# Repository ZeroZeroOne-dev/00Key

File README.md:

# 001Key

Custom 75% Keyboard.

## Hardware

- Teensy 4.1 development board
- SSD1306 0.96 Inch OLED Display
- MX & Alps switch support
- Backlight (single color) support
- RGB Underglow support

## Firmware

Custom firmware, has layer, OLED, Backlight, Underglow support

## OLED display

Displays currently shows

- capslock status
- Selected layer
- backlight intensity 
- Underglow collor selection (RGB Values)

## Underglow

3 Effects
- Solid color
- Rotating rainbow
- Off

## PCB

- Designed in kicad
- Used freerouting for traces

## Backplate

- Designed in FreeCAD
- Spaced from PCB with (10mm) standoffs
- STL files included for 3D printing in 2 parts

## Case

Stacked acrylic case

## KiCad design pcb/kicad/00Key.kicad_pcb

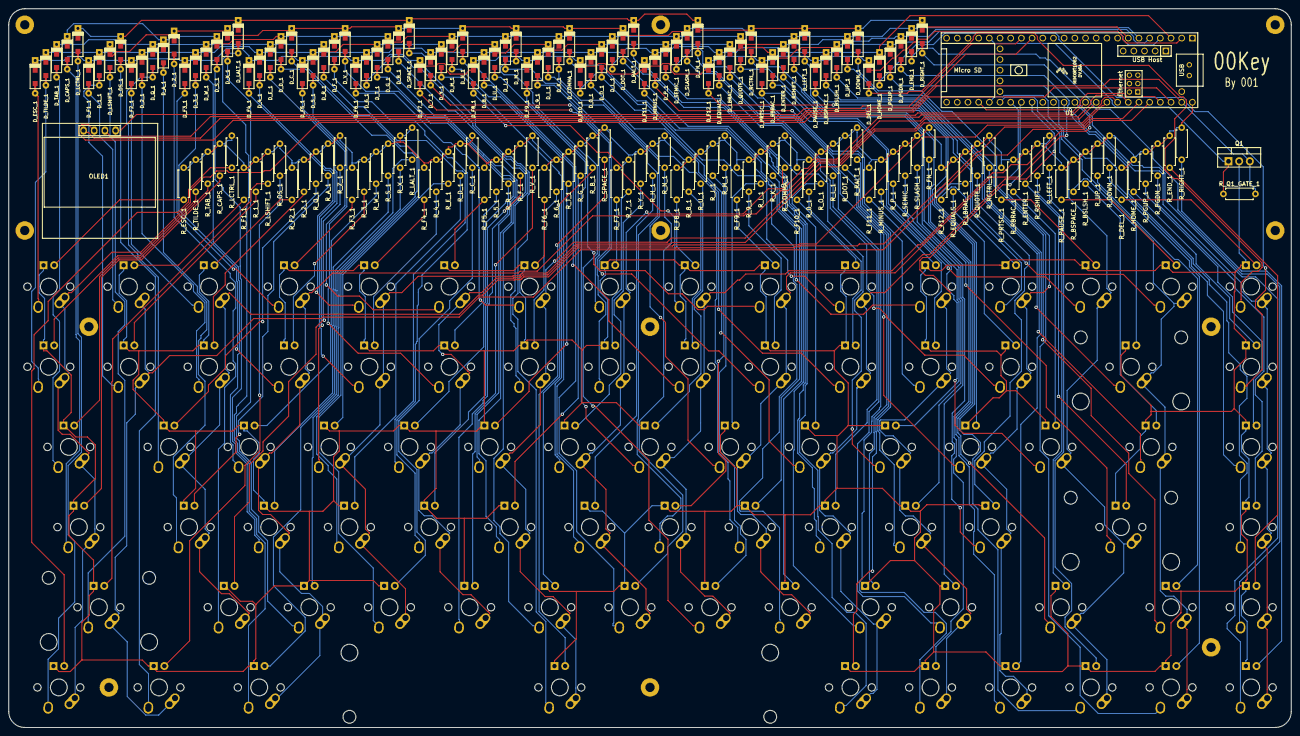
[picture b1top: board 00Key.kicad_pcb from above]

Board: 2 copper layers, 304.8 x 170.8 mm, 268 parts (0 on the bottom side), 197 nets.

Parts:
D_0_1, D_1_1, D_2_1, D_3_1, D_4_1, D_5_1, D_6_1, D_7_1, D_8_1, D_9_1: D; D_SOD123_axial
D_A_1: D; D_SOD123_axial
D_BSLSH_1: D; D_SOD123_axial
D_BSPACE_1: D; D_SOD123_axial
D_B_1: D; D_SOD123_axial
D_CAPS_1: D; D_SOD123_axial
D_COMMA_1: D; D_SOD123_axial
D_C_1: D; D_SOD123_axial
D_DEL_1: D; D_SOD123_axial
D_DOT_1: D; D_SOD123_axial
D_DOWN_1: D; D_SOD123_axial
D_D_1: D; D_SOD123_axial
D_END_1: D; D_SOD123_axial
D_ENTER_1: D; D_SOD123_axial
D_EQUALS_1: D; D_SOD123_axial
D_ESC_1: D; D_SOD123_axial
D_E_1: D; D_SOD123_axial
D_F1_1, D_F2_1, D_F3_1, D_F4_1, D_F5_1, D_F6_1, D_F7_1, D_F8_1, D_F9_1, D_F10_1, D_F11_1, D_F12_1: D; D_SOD123_axial
D_FN_1: D; D_SOD123_axial
D_F_1: D; D_SOD123_axial
D_G_1: D; D_SOD123_axial
D_HOME_1: D; D_SOD123_axial
D_H_1: D; D_SOD123_axial
D_I_1: D; D_SOD123_axial
D_J_1: D; D_SOD123_axial
D_K_1: D; D_SOD123_axial
D_LALT_1: D; D_SOD123_axial
D_LBRAC_1: D; D_SOD123_axial
D_LCTRL_1: D; D_SOD123_axial
D_LEFT_1: D; D_SOD123_axial
D_LSHIFT_1: D; D_SOD123_axial
D_L_1: D; D_SOD123_axial
D_MINUS_1: D; D_SOD123_axial
D_M_1: D; D_SOD123_axial
D_N_1: D; D_SOD123_axial
D_OS_1: D; D_SOD123_axial
D_O_1: D; D_SOD123_axial
D_PAUSE_1: D; D_SOD123_axial
D_PGDN_1: D; D_SOD123_axial
D_PGUP_1: D; D_SOD123_axial
D_PRTSC_1: D; D_SOD123_axial
D_P_1: D; D_SOD123_axial
D_QUOTE_1: D; D_SOD123_axial
D_Q_1: D; D_SOD123_axial
D_RALT_1: D; D_SOD123_axial
D_RBRAC_1: D; D_SOD123_axial
D_RCTRL_1: D; D_SOD123_axial
D_RIGHT_1: D; D_SOD123_axial
D_RSHIFT_1: D; D_SOD123_axial
D_R_1: D; D_SOD123_axial
D_SEMIC_1: D; D_SOD123_axial
D_SLASH_1: D; D_SOD123_axial
D_SPACE_1: D; D_SOD123_axial
D_S_1: D; D_SOD123_axial
D_TAB_1: D; D_SOD123_axial
D_TILDE_1: D; D_SOD123_axial
D_T_1: D; D_SOD123_axial
D_UP_1: D; D_SOD123_axial
D_U_1: D; D_SOD123_axial
D_V_1: D; D_SOD123_axial
D_W_1: D; D_SOD123_axial
D_X_1: D; D_SOD123_axial
D_Y_1: D; D_SOD123_axial
D_Z_1: D; D_SOD123_axial
H_KEYS_BL: MountingHole_2.2mm_M2_Pad
H_KEYS_BM: MountingHole_2.2mm_M2_Pad
H_KEYS_BR: MountingHole_2.2mm_M2_Pad
H_KEYS_TL: MountingHole_2.2mm_M2_Pad
H_KEYS_TM: MountingHole_2.2mm_M2_Pad
H_KEYS_TR: MountingHole_2.2mm_M2_Pad
H_PLATE_BL: MountingHole_2.2mm_M2_Pad
H_PLATE_BR: MountingHole_2.2mm_M2_Pad
H_PLATE_MB: MountingHole_2.2mm_M2_Pad
H_PLATE_TL: MountingHole_2.2mm_M2_Pad
H_PLATE_TM: MountingHole_2.2mm_M2_Pad
H_PLATE_TR: MountingHole_2.2mm_M2_Pad
MX_0_1, MX_1_1, MX_2_1, MX_3_1, MX_4_1, MX_5_1, MX_6_1, MX_7_1, MX_8_1, MX_9_1: MX-LED; MX-1U
MX_A_1: MX-LED; MX-1U
MX_BSLSH_1: MX-LED; MX-1.5U
MX_BSPACE_1: MX-LED; MX-2U-ReversedStabilizers
MX_B_1: MX-LED; MX-1U
MX_CAPS_1: MX-LED; MX-1.75U
MX_COMMA_1: MX-LED; MX-1U
MX_C_1: MX-LED; MX-1U
MX_DEL_1: MX-LED; MX-1U
MX_DOT_1: MX-LED; MX-1U
MX_DOWN_1: MX-LED; MX-1U
MX_D_1: MX-LED; MX-1U
MX_END_1: MX-LED; MX-1U
MX_ENTER_1: MX-LED; MX-2.25U-ReversedStabilizers
MX_EQUALS_1: MX-LED; MX-1U
MX_ESC_1: MX-LED; MX-1U
MX_E_1: MX-LED; MX-1U
MX_F1_1, MX_F2_1, MX_F3_1, MX_F4_1, MX_F5_1, MX_F6_1, MX_F7_1, MX_F8_1, MX_F9_1, MX_F10_1, MX_F11_1, MX_F12_1: MX-LED; MX-1U
MX_FN_1: MX-LED; MX-1U
MX_F_1: MX-LED; MX-1U
MX_G_1: MX-LED; MX-1U
MX_HOME_1: MX-LED; MX-1U
MX_H_1: MX-LED; MX-1U
MX_I_1: MX-LED; MX-1U
MX_J_1: MX-LED; MX-1U
MX_K_1: MX-LED; MX-1U
MX_LALT_1: MX-LED; MX-1.25U
MX_LBRAC_1: MX-LED; MX-1U
MX_LCTRL_1: MX-LED; MX-1.25U
MX_LEFT_1: MX-LED; MX-1U
MX_LSHIFT_1: MX-LED; MX-2.25U-ReversedStabilizers
MX_L_1: MX-LED; MX-1U
MX_MINUS_1: MX-LED; MX-1U
MX_M_1: MX-LED; MX-1U
MX_N_1: MX-LED; MX-1U
MX_OS_1: MX-LED; MX-1.25U
MX_O_1: MX-LED; MX-1U
MX_PAUSE_1: MX-LED; MX-1U
MX_PGDN_1: MX-LED; MX-1U
MX_PGUP_1: MX-LED; MX-1U
MX_PRTSC_1: MX-LED; MX-1U
MX_P_1: MX-LED; MX-1U
MX_QUOTE_1: MX-LED; MX-1U
MX_Q_1: MX-LED; MX-1U
MX_RALT_1: MX-LED; MX-1U
MX_RBRAC_1: MX-LED; MX-1U
MX_RCTRL_1: MX-LED; MX-1U
MX_RIGHT_1: MX-LED; MX-1U
MX_RSHIFT_1: MX-LED; MX-1.75U
MX_R_1: MX-LED; MX-1U
MX_SEMIC_1: MX-LED; MX-1U
MX_SLASH_1: MX-LED; MX-1U
MX_SPACE_1: MX-LED; MX-6.25U
MX_S_1: MX-LED; MX-1U
MX_TAB_1: MX-LED; MX-1.5U
MX_TILDE_1: MX-LED; MX-1U
MX_T_1: MX-LED; MX-1U
MX_UP_1: MX-LED; MX-1U
MX_U_1: MX-LED; MX-1U
MX_V_1: MX-LED; MX-1U
MX_W_1: MX-LED; MX-1U
MX_X_1: MX-LED; MX-1U
MX_Y_1: MX-LED; MX-1U
MX_Z_1: MX-LED; MX-1U
OLED1: SSD1306; 128x64OLED
Q1: IRLZ44N; TO-220-3_Vertical
R_0_1, R_1_1, R_2_1, R_3_1, R_4_1, R_5_1, R_6_1, R_7_1, R_8_1, R_9_1: 470; R_Axial_DIN0207_L6.3mm_D2.5mm_P7.62mm_Horizontal
R_A_1: 470; R_Axial_DIN0207_L6.3mm_D2.5mm_P7.62mm_Horizontal
R_BSLSH_1: 470; R_Axial_DIN0207_L6.3mm_D2.5mm_P7.62mm_Horizontal
R_BSPACE_1: 470; R_Axial_DIN0207_L6.3mm_D2.5mm_P7.62mm_Horizontal
R_B_1: 470; R_Axial_DIN0207_L6.3mm_D2.5mm_P7.62mm_Horizontal
R_CAPS_1: 470; R_Axial_DIN0207_L6.3mm_D2.5mm_P7.62mm_Horizontal
R_COMMA_1: 470; R_Axial_DIN0207_L6.3mm_D2.5mm_P7.62mm_Horizontal
R_C_1: 470; R_Axial_DIN0207_L6.3mm_D2.5mm_P7.62mm_Horizontal
R_DEL_1: 470; R_Axial_DIN0207_L6.3mm_D2.5mm_P7.62mm_Horizontal
R_DOT_1: 470; R_Axial_DIN0207_L6.3mm_D2.5mm_P7.62mm_Horizontal
R_DOWN_1: 470; R_Axial_DIN0207_L6.3mm_D2.5mm_P7.62mm_Horizontal
R_D_1: 470; R_Axial_DIN0207_L6.3mm_D2.5mm_P7.62mm_Horizontal
R_END_1: 470; R_Axial_DIN0207_L6.3mm_D2.5mm_P7.62mm_Horizontal
R_ENTER_1: 470; R_Axial_DIN0207_L6.3mm_D2.5mm_P7.62mm_Horizontal
R_EQUALS_1: 470; R_Axial_DIN0207_L6.3mm_D2.5mm_P7.62mm_Horizontal
R_ESC_1: 470; R_Axial_DIN0207_L6.3mm_D2.5mm_P7.62mm_Horizontal
R_E_1: 470; R_Axial_DIN0207_L6.3mm_D2.5mm_P7.62mm_Horizontal
R_F1_1, R_F2_1, R_F3_1, R_F4_1, R_F5_1, R_F6_1, R_F7_1, R_F8_1, R_F9_1, R_F10_1, R_F11_1, R_F12_1: 470; R_Axial_DIN0207_L6.3mm_D2.5mm_P7.62mm_Horizontal
R_FN_1: 470; R_Axial_DIN0207_L6.3mm_D2.5mm_P7.62mm_Horizontal
R_F_1: 470; R_Axial_DIN0207_L6.3mm_D2.5mm_P7.62mm_Horizontal
R_G_1: 470; R_Axial_DIN0207_L6.3mm_D2.5mm_P7.62mm_Horizontal
R_HOME_1: 470; R_Axial_DIN0207_L6.3mm_D2.5mm_P7.62mm_Horizontal
R_H_1: 470; R_Axial_DIN0207_L6.3mm_D2.5mm_P7.62mm_Horizontal
R_I_1: 470; R_Axial_DIN0207_L6.3mm_D2.5mm_P7.62mm_Horizontal
R_J_1: 470; R_Axial_DIN0207_L6.3mm_D2.5mm_P7.62mm_Horizontal
R_K_1: 470; R_Axial_DIN0207_L6.3mm_D2.5mm_P7.62mm_Horizontal
R_LALT_1: 470; R_Axial_DIN0207_L6.3mm_D2.5mm_P7.62mm_Horizontal
R_LBRAC_1: 470; R_Axial_DIN0207_L6.3mm_D2.5mm_P7.62mm_Horizontal
R_LCTRL_1: 470; R_Axial_DIN0207_L6.3mm_D2.5mm_P7.62mm_Horizontal
R_LEFT_1: 470; R_Axial_DIN0207_L6.3mm_D2.5mm_P7.62mm_Horizontal
R_LSHIFT_1: 470; R_Axial_DIN0207_L6.3mm_D2.5mm_P7.62mm_Horizontal
R_L_1: 470; R_Axial_DIN0207_L6.3mm_D2.5mm_P7.62mm_Horizontal
R_MINUS_1: 470; R_Axial_DIN0207_L6.3mm_D2.5mm_P7.62mm_Horizontal
R_M_1: 470; R_Axial_DIN0207_L6.3mm_D2.5mm_P7.62mm_Horizontal
R_N_1: 470; R_Axial_DIN0207_L6.3mm_D2.5mm_P7.62mm_Horizontal
R_OS_1: 470; R_Axial_DIN0207_L6.3mm_D2.5mm_P7.62mm_Horizontal
R_O_1: 470; R_Axial_DIN0207_L6.3mm_D2.5mm_P7.62mm_Horizontal
R_PAUSE_1: 470; R_Axial_DIN0207_L6.3mm_D2.5mm_P7.62mm_Horizontal
R_PGDN_1: 470; R_Axial_DIN0207_L6.3mm_D2.5mm_P7.62mm_Horizontal
R_PGUP_1: 470; R_Axial_DIN0207_L6.3mm_D2.5mm_P7.62mm_Horizontal
R_PRTSC_1: 470; R_Axial_DIN0207_L6.3mm_D2.5mm_P7.62mm_Horizontal
R_P_1: 470; R_Axial_DIN0207_L6.3mm_D2.5mm_P7.62mm_Horizontal
R_Q1_GATE_1: 10K; R_Axial_DIN0207_L6.3mm_D2.5mm_P7.62mm_Horizontal
R_QUOTE_1: 470; R_Axial_DIN0207_L6.3mm_D2.5mm_P7.62mm_Horizontal
R_Q_1: 470; R_Axial_DIN0207_L6.3mm_D2.5mm_P7.62mm_Horizontal
R_RALT_1: 470; R_Axial_DIN0207_L6.3mm_D2.5mm_P7.62mm_Horizontal
R_RBRAC_1: 470; R_Axial_DIN0207_L6.3mm_D2.5mm_P7.62mm_Horizontal
R_RCTRL_1: 470; R_Axial_DIN0207_L6.3mm_D2.5mm_P7.62mm_Horizontal
R_RIGHT_1: 470; R_Axial_DIN0207_L6.3mm_D2.5mm_P7.62mm_Horizontal
R_RSHIFT_1: 470; R_Axial_DIN0207_L6.3mm_D2.5mm_P7.62mm_Horizontal
R_R_1: 470; R_Axial_DIN0207_L6.3mm_D2.5mm_P7.62mm_Horizontal
R_SEMIC_1: 470; R_Axial_DIN0207_L6.3mm_D2.5mm_P7.62mm_Horizontal
R_SLASH_1: 470; R_Axial_DIN0207_L6.3mm_D2.5mm_P7.62mm_Horizontal
R_SPACE_1: 470; R_Axial_DIN0207_L6.3mm_D2.5mm_P7.62mm_Horizontal
R_S_1: 470; R_Axial_DIN0207_L6.3mm_D2.5mm_P7.62mm_Horizontal
R_TAB_1: 470; R_Axial_DIN0207_L6.3mm_D2.5mm_P7.62mm_Horizontal
R_TILDE_1: 470; R_Axial_DIN0207_L6.3mm_D2.5mm_P7.62mm_Horizontal
R_T_1: 470; R_Axial_DIN0207_L6.3mm_D2.5mm_P7.62mm_Horizontal
R_UP_1: 470; R_Axial_DIN0207_L6.3mm_D2.5mm_P7.62mm_Horizontal
R_U_1: 470; R_Axial_DIN0207_L6.3mm_D2.5mm_P7.62mm_Horizontal
R_V_1: 470; R_Axial_DIN0207_L6.3mm_D2.5mm_P7.62mm_Horizontal
R_W_1: 470; R_Axial_DIN0207_L6.3mm_D2.5mm_P7.62mm_Horizontal
R_X_1: 470; R_Axial_DIN0207_L6.3mm_D2.5mm_P7.62mm_Horizontal
R_Y_1: 470; R_Axial_DIN0207_L6.3mm_D2.5mm_P7.62mm_Horizontal
R_Z_1: 470; R_Axial_DIN0207_L6.3mm_D2.5mm_P7.62mm_Horizontal
U1: Teensy4.1; Teensy41

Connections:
3.3V: OLED1.2, U1.46
5V: R_0_1.2, R_1_1.2, R_2_1.2, R_3_1.2, R_4_1.2, R_5_1.2, R_6_1.2, R_7_1.2, R_8_1.2, R_9_1.2, R_A_1.2, R_BSLSH_1.2, R_BSPACE_1.2, R_B_1.2, R_CAPS_1.2, R_COMMA_1.2, R_C_1.2, R_DEL_1.2, R_DOT_1.2, R_DOWN_1.2, R_D_1.2, R_END_1.2, R_ENTER_1.2, R_EQUALS_1.2, R_ESC_1.2, R_E_1.2, R_F1_1.2, R_F2_1.2, R_F3_1.2, R_F4_1.2, R_F5_1.2, R_F6_1.2, R_F7_1.2, R_F8_1.2, R_F9_1.2, R_F10_1.2, R_F11_1.2, R_F12_1.2, R_FN_1.2, R_F_1.2, R_G_1.2, R_HOME_1.2, R_H_1.2, R_I_1.2, R_J_1.2, R_K_1.2, R_LALT_1.2, R_LBRAC_1.2, R_LCTRL_1.2, R_LEFT_1.2, R_LSHIFT_1.2, R_L_1.2, R_MINUS_1.2, R_M_1.2, R_N_1.2, R_OS_1.2, R_O_1.2, R_PAUSE_1.2, R_PGDN_1.2, R_PGUP_1.2, R_PRTSC_1.2, R_P_1.2, R_QUOTE_1.2, R_Q_1.2, R_RALT_1.2, R_RBRAC_1.2, R_RCTRL_1.2, R_RIGHT_1.2, R_RSHIFT_1.2, R_R_1.2, R_SEMIC_1.2, R_SLASH_1.2, R_SPACE_1.2, R_S_1.2, R_TAB_1.2, R_TILDE_1.2, R_T_1.2, R_UP_1.2, R_U_1.2, R_V_1.2, R_W_1.2, R_X_1.2, R_Y_1.2, R_Z_1.2, U1.48
GND: OLED1.1, Q1.3, R_Q1_GATE_1.2, U1.47
LEDGND: MX_0_1.4, MX_1_1.4, MX_2_1.4, MX_3_1.4, MX_4_1.4, MX_5_1.4, MX_6_1.4, MX_7_1.4, MX_8_1.4, MX_9_1.4, MX_A_1.4, MX_BSLSH_1.4, MX_BSPACE_1.4, MX_B_1.4, MX_CAPS_1.4, MX_COMMA_1.4, MX_C_1.4, MX_DEL_1.4, MX_DOT_1.4, MX_DOWN_1.4, MX_D_1.4, MX_END_1.4, MX_ENTER_1.4, MX_EQUALS_1.4, MX_ESC_1.4, MX_E_1.4, MX_F1_1.4, MX_F2_1.4, MX_F3_1.4, MX_F4_1.4, MX_F5_1.4, MX_F6_1.4, MX_F7_1.4, MX_F8_1.4, MX_F9_1.4, MX_F10_1.4, MX_F11_1.4, MX_F12_1.4, MX_FN_1.4, MX_F_1.4, MX_G_1.4, MX_HOME_1.4, MX_H_1.4, MX_I_1.4, MX_J_1.4, MX_K_1.4, MX_LALT_1.4, MX_LBRAC_1.4, MX_LCTRL_1.4, MX_LEFT_1.4, MX_LSHIFT_1.4, MX_L_1.4, MX_MINUS_1.4, MX_M_1.4, MX_N_1.4, MX_OS_1.4, MX_O_1.4, MX_PAUSE_1.4, MX_PGDN_1.4, MX_PGUP_1.4, MX_PRTSC_1.4, MX_P_1.4, MX_QUOTE_1.4, MX_Q_1.4, MX_RALT_1.4, MX_RBRAC_1.4, MX_RCTRL_1.4, MX_RIGHT_1.4, MX_RSHIFT_1.4, MX_R_1.4, MX_SEMIC_1.4, MX_SLASH_1.4, MX_SPACE_1.4, MX_S_1.4, MX_TAB_1.4, MX_TILDE_1.4, MX_T_1.4, MX_UP_1.4, MX_U_1.4, MX_V_1.4, MX_W_1.4, MX_X_1.4, MX_Y_1.4, MX_Z_1.4, Q1.2
LEDPWM: Q1.1, R_Q1_GATE_1.1, U1.20
unnamed: D_0_1.2, MX_0_1.2
unnamed: D_1_1.2, MX_1_1.2
unnamed: D_2_1.2, MX_2_1.2
unnamed: D_3_1.2, MX_3_1.2
unnamed: D_4_1.2, MX_4_1.2
unnamed: D_5_1.2, MX_5_1.2
unnamed: D_6_1.2, MX_6_1.2
unnamed: D_7_1.2, MX_7_1.2
unnamed: D_8_1.2, MX_8_1.2
unnamed: D_9_1.2, MX_9_1.2
unnamed: D_A_1.2, MX_A_1.2
unnamed: D_BSLSH_1.2, MX_BSLSH_1.2
unnamed: D_BSPACE_1.2, MX_BSPACE_1.2
unnamed: D_B_1.2, MX_B_1.2
unnamed: D_CAPS_1.2, MX_CAPS_1.2
unnamed: D_COMMA_1.2, MX_COMMA_1.2
unnamed: D_C_1.2, MX_C_1.2
unnamed: D_DEL_1.2, MX_DEL_1.2
unnamed: D_DOT_1.2, MX_DOT_1.2
unnamed: D_DOWN_1.2, MX_DOWN_1.2
unnamed: D_D_1.2, MX_D_1.2
unnamed: D_END_1.2, MX_END_1.2
unnamed: D_ENTER_1.2, MX_ENTER_1.2
unnamed: D_EQUALS_1.2, MX_EQUALS_1.2
unnamed: D_ESC_1.2, MX_ESC_1.2
unnamed: D_E_1.2, MX_E_1.2
unnamed: D_F1_1.2, MX_F1_1.2
unnamed: D_F2_1.2, MX_F2_1.2
unnamed: D_F3_1.2, MX_F3_1.2
unnamed: D_F4_1.2, MX_F4_1.2
unnamed: D_F5_1.2, MX_F5_1.2
unnamed: D_F6_1.2, MX_F6_1.2
unnamed: D_F7_1.2, MX_F7_1.2
unnamed: D_F8_1.2, MX_F8_1.2
unnamed: D_F9_1.2, MX_F9_1.2
unnamed: D_F10_1.2, MX_F10_1.2
unnamed: D_F11_1.2, MX_F11_1.2
unnamed: D_F12_1.2, MX_F12_1.2
unnamed: D_FN_1.2, MX_FN_1.2
unnamed: D_F_1.2, MX_F_1.2
unnamed: D_G_1.2, MX_G_1.2
unnamed: D_HOME_1.2, MX_HOME_1.2
unnamed: D_H_1.2, MX_H_1.2
unnamed: D_I_1.2, MX_I_1.2
unnamed: D_J_1.2, MX_J_1.2
unnamed: D_K_1.2, MX_K_1.2
unnamed: D_LALT_1.2, MX_LALT_1.2
unnamed: D_LBRAC_1.2, MX_LBRAC_1.2
unnamed: D_LCTRL_1.2, MX_LCTRL_1.2
unnamed: D_LEFT_1.2, MX_LEFT_1.2
unnamed: D_LSHIFT_1.2, MX_LSHIFT_1.2
unnamed: D_L_1.2, MX_L_1.2
unnamed: D_MINUS_1.2, MX_MINUS_1.2
unnamed: D_M_1.2, MX_M_1.2
unnamed: D_N_1.2, MX_N_1.2
unnamed: D_OS_1.2, MX_OS_1.2
unnamed: D_O_1.2, MX_O_1.2
unnamed: D_PAUSE_1.2, MX_PAUSE_1.2
unnamed: D_PGDN_1.2, MX_PGDN_1.2
unnamed: D_PGUP_1.2, MX_PGUP_1.2
unnamed: D_PRTSC_1.2, MX_PRTSC_1.2
unnamed: D_P_1.2, MX_P_1.2
unnamed: D_QUOTE_1.2, MX_QUOTE_1.2
unnamed: D_Q_1.2, MX_Q_1.2
unnamed: D_RALT_1.2, MX_RALT_1.2
unnamed: D_RBRAC_1.2, MX_RBRAC_1.2
unnamed: D_RCTRL_1.2, MX_RCTRL_1.2
unnamed: D_RIGHT_1.2, MX_RIGHT_1.2
unnamed: D_RSHIFT_1.2, MX_RSHIFT_1.2
unnamed: D_R_1.2, MX_R_1.2
unnamed: D_SEMIC_1.2, MX_SEMIC_1.2
unnamed: D_SLASH_1.2, MX_SLASH_1.2
unnamed: D_SPACE_1.2, MX_SPACE_1.2
unnamed: D_S_1.2, MX_S_1.2
unnamed: D_TAB_1.2, MX_TAB_1.2
unnamed: D_TILDE_1.2, MX_TILDE_1.2
unnamed: D_T_1.2, MX_T_1.2
unnamed: D_UP_1.2, MX_UP_1.2
unnamed: D_U_1.2, MX_U_1.2
unnamed: D_V_1.2, MX_V_1.2
unnamed: D_W_1.2, MX_W_1.2
unnamed: D_X_1.2, MX_X_1.2
unnamed: D_Y_1.2, MX_Y_1.2
unnamed: D_Z_1.2, MX_Z_1.2
unnamed: MX_0_1.3, R_0_1.1
unnamed: MX_1_1.3, R_1_1.1
unnamed: MX_2_1.3, R_2_1.1
unnamed: MX_3_1.3, R_3_1.1
unnamed: MX_4_1.3, R_4_1.1
unnamed: MX_5_1.3, R_5_1.1
unnamed: MX_6_1.3, R_6_1.1
unnamed: MX_7_1.3, R_7_1.1
unnamed: MX_8_1.3, R_8_1.1
unnamed: MX_9_1.3, R_9_1.1
unnamed: MX_A_1.3, R_A_1.1
unnamed: MX_BSLSH_1.3, R_BSLSH_1.1
unnamed: MX_BSPACE_1.3, R_BSPACE_1.1
unnamed: MX_B_1.3, R_B_1.1
unnamed: MX_CAPS_1.3, R_CAPS_1.1
unnamed: MX_COMMA_1.3, R_COMMA_1.1
unnamed: MX_C_1.3, R_C_1.1
unnamed: MX_DEL_1.3, R_DEL_1.1
unnamed: MX_DOT_1.3, R_DOT_1.1
unnamed: MX_DOWN_1.3, R_DOWN_1.1
unnamed: MX_D_1.3, R_D_1.1
unnamed: MX_END_1.3, R_END_1.1
unnamed: MX_ENTER_1.3, R_ENTER_1.1
unnamed: MX_EQUALS_1.3, R_EQUALS_1.1
unnamed: MX_ESC_1.3, R_ESC_1.1
unnamed: MX_E_1.3, R_E_1.1
unnamed: MX_F1_1.3, R_F1_1.1
unnamed: MX_F2_1.3, R_F2_1.1
unnamed: MX_F3_1.3, R_F3_1.1
unnamed: MX_F4_1.3, R_F4_1.1
unnamed: MX_F5_1.3, R_F5_1.1
unnamed: MX_F6_1.3, R_F6_1.1
unnamed: MX_F7_1.3, R_F7_1.1
unnamed: MX_F8_1.3, R_F8_1.1
unnamed: MX_F9_1.3, R_F9_1.1
unnamed: MX_F10_1.3, R_F10_1.1
unnamed: MX_F11_1.3, R_F11_1.1
unnamed: MX_F12_1.3, R_F12_1.1
unnamed: MX_FN_1.3, R_FN_1.1
unnamed: MX_F_1.3, R_F_1.1
unnamed: MX_G_1.3, R_G_1.1
unnamed: MX_HOME_1.3, R_HOME_1.1
unnamed: MX_H_1.3, R_H_1.1
unnamed: MX_I_1.3, R_I_1.1
unnamed: MX_J_1.3, R_J_1.1
unnamed: MX_K_1.3, R_K_1.1
unnamed: MX_LALT_1.3, R_LALT_1.1
unnamed: MX_LBRAC_1.3, R_LBRAC_1.1
unnamed: MX_LCTRL_1.3, R_LCTRL_1.1
unnamed: MX_LEFT_1.3, R_LEFT_1.1
unnamed: MX_LSHIFT_1.3, R_LSHIFT_1.1
unnamed: MX_L_1.3, R_L_1.1
unnamed: MX_MINUS_1.3, R_MINUS_1.1
unnamed: MX_M_1.3, R_M_1.1
unnamed: MX_N_1.3, R_N_1.1
unnamed: MX_OS_1.3, R_OS_1.1
unnamed: MX_O_1.3, R_O_1.1
unnamed: MX_PAUSE_1.3, R_PAUSE_1.1
unnamed: MX_PGDN_1.3, R_PGDN_1.1
unnamed: MX_PGUP_1.3, R_PGUP_1.1
unnamed: MX_PRTSC_1.3, R_PRTSC_1.1
unnamed: MX_P_1.3, R_P_1.1
unnamed: MX_QUOTE_1.3, R_QUOTE_1.1
unnamed: MX_Q_1.3, R_Q_1.1
unnamed: MX_RALT_1.3, R_RALT_1.1
unnamed: MX_RBRAC_1.3, R_RBRAC_1.1
unnamed: MX_RCTRL_1.3, R_RCTRL_1.1
unnamed: MX_RIGHT_1.3, R_RIGHT_1.1
unnamed: MX_RSHIFT_1.3, R_RSHIFT_1.1
unnamed: MX_R_1.3, R_R_1.1
unnamed: MX_SEMIC_1.3, R_SEMIC_1.1
unnamed: MX_SLASH_1.3, R_SLASH_1.1
unnamed: MX_SPACE_1.3, R_SPACE_1.1
unnamed: MX_S_1.3, R_S_1.1
unnamed: MX_TAB_1.3, R_TAB_1.1
unnamed: MX_TILDE_1.3, R_TILDE_1.1
unnamed: MX_T_1.3, R_T_1.1
unnamed: MX_UP_1.3, R_UP_1.1
unnamed: MX_U_1.3, R_U_1.1
unnamed: MX_V_1.3, R_V_1.1
unnamed: MX_W_1.3, R_W_1.1
unnamed: MX_X_1.3, R_X_1.1
unnamed: MX_Y_1.3, R_Y_1.1
unnamed: MX_Z_1.3, R_Z_1.1
OLEDSCL: OLED1.3, U1.16
OLEDSDA: OLED1.4, U1.17
col0: MX_CAPS_1.1, MX_ESC_1.1, MX_LCTRL_1.1, MX_TAB_1.1, MX_TILDE_1.1, U1.45
col1: MX_1_1.1, MX_F1_1.1, MX_LSHIFT_1.1, MX_OS_1.1, U1.44
col2: MX_2_1.1, MX_A_1.1, MX_F2_1.1, MX_Q_1.1, MX_Z_1.1, U1.43
col3: MX_3_1.1, MX_F3_1.1, MX_LALT_1.1, MX_S_1.1, MX_W_1.1, MX_X_1.1, U1.42
col4: MX_4_1.1, MX_C_1.1, MX_D_1.1, MX_E_1.1, MX_F4_1.1, U1.41
col5: MX_5_1.1, MX_F5_1.1, MX_F_1.1, MX_R_1.1, MX_V_1.1, U1.40
col6: MX_6_1.1, MX_B_1.1, MX_F6_1.1, MX_G_1.1, MX_SPACE_1.1, MX_T_1.1, U1.39
col7: MX_7_1.1, MX_F7_1.1, MX_H_1.1, MX_N_1.1, MX_Y_1.1, U1.38
col8: MX_8_1.1, MX_F8_1.1, MX_J_1.1, MX_M_1.1, MX_U_1.1, U1.37
col9: MX_9_1.1, MX_COMMA_1.1, MX_F9_1.1, MX_I_1.1, MX_K_1.1, U1.36
col10: MX_0_1.1, MX_DOT_1.1, MX_F10_1.1, MX_L_1.1, MX_O_1.1, MX_RALT_1.1, U1.33
col11: MX_F11_1.1, MX_FN_1.1, MX_MINUS_1.1, MX_P_1.1, MX_SEMIC_1.1, MX_SLASH_1.1, U1.32
col12: MX_EQUALS_1.1, MX_F12_1.1, MX_LBRAC_1.1, MX_QUOTE_1.1, MX_RCTRL_1.1, U1.31
col13: MX_ENTER_1.1, MX_LEFT_1.1, MX_PRTSC_1.1, MX_RBRAC_1.1, MX_RSHIFT_1.1, U1.30
col14: MX_BSLSH_1.1, MX_BSPACE_1.1, MX_DOWN_1.1, MX_PAUSE_1.1, MX_UP_1.1, U1.29
col15: MX_DEL_1.1, MX_END_1.1, MX_HOME_1.1, MX_PGDN_1.1, MX_PGUP_1.1, MX_RIGHT_1.1, U1.28
row0: D_DEL_1.1, D_ESC_1.1, D_F1_1.1, D_F2_1.1, D_F3_1.1, D_F4_1.1, D_F5_1.1, D_F6_1.1, D_F7_1.1, D_F8_1.1, D_F9_1.1, D_F10_1.1, D_F11_1.1, D_F12_1.1, D_PAUSE_1.1, D_PRTSC_1.1, U1.2
row1: D_0_1.1, D_1_1.1, D_2_1.1, D_3_1.1, D_4_1.1, D_5_1.1, D_6_1.1, D_7_1.1, D_8_1.1, D_9_1.1, D_BSPACE_1.1, D_EQUALS_1.1, D_HOME_1.1, D_MINUS_1.1, D_TILDE_1.1, U1.3
row2: D_BSLSH_1.1, D_E_1.1, D_I_1.1, D_LBRAC_1.1, D_O_1.1, D_PGUP_1.1, D_P_1.1, D_Q_1.1, D_RBRAC_1.1, D_R_1.1, D_TAB_1.1, D_T_1.1, D_U_1.1, D_W_1.1, D_Y_1.1, U1.4
row3: D_A_1.1, D_CAPS_1.1, D_D_1.1, D_ENTER_1.1, D_F_1.1, D_G_1.1, D_H_1.1, D_J_1.1, D_K_1.1, D_L_1.1, D_PGDN_1.1, D_QUOTE_1.1, D_SEMIC_1.1, D_S_1.1, U1.5
row4: D_B_1.1, D_COMMA_1.1, D_C_1.1, D_DOT_1.1, D_END_1.1, D_LSHIFT_1.1, D_M_1.1, D_N_1.1, D_RSHIFT_1.1, D_SLASH_1.1, D_UP_1.1, D_V_1.1, D_X_1.1, D_Z_1.1, U1.6
row5: D_DOWN_1.1, D_FN_1.1, D_LALT_1.1, D_LCTRL_1.1, D_LEFT_1.1, D_OS_1.1, D_RALT_1.1, D_RCTRL_1.1, D_RIGHT_1.1, D_SPACE_1.1, U1.7

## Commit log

2020-08-24 init
2020-08-24 basic keyboard
2020-08-25 this doesnt work
2020-08-25 basics
2020-08-26 with debounce
2020-08-26 no debounce
2020-08-26 move
2020-08-26 clean
2020-08-26 oled basics working
2020-08-27 cleaner keymap
2020-08-27 pre teensy
2020-08-27 teensy keyboard working
2020-08-27 OLED working with teensy
2020-08-29 region includes declarations
2020-08-29 key status saved
2020-08-29 actions start
2020-08-29 layer switching
2020-08-29 layer switching working
2020-08-29 backlight
2020-09-17 Library updates
2020-09-17 need more space for caps lock indicator
2020-09-17 caps lock indicator
2020-09-17 prototype entry
2020-09-21 initial PCB
2020-09-21 added switches and diodes
2020-09-21 connected rows and columns
2020-09-23 why does kicad need numbered annotation? ugh
2020-09-23 added number to annotations
2020-09-23 adding submodules
2020-09-24 submodules
2020-09-24 replaced with MX switches
2020-09-25 correct key sizes
2020-09-26 labels
2020-09-26 led resistor values
2020-09-26 Resistor footprints
2020-09-27 oled
2020-09-28 missing connection
2020-09-28 keyboard layout in pcb
2020-09-30 diodes layout
2020-10-01 start resistor placement
2020-10-04 first layout
2020-10-04 safe
2020-10-04 pulldown resistor mosfet
2020-10-04 switches upside down
2020-10-04 reversed stabs
2020-10-04 reversed space stab
2020-10-04 edge cuts, first mouthing holes
2020-10-09 moving stuff around
2020-10-09 logo
2020-10-10 holes
2020-10-10 hole labels
2020-10-10 corner radius
2020-10-12 traces
2020-10-13 render
2020-10-13 removed folders so submodules work
2020-10-13 moved pcb
2020-10-13 submodules move
2020-10-18 basic plate design
2020-10-22 Basic plate
2020-10-23 plate stls
2020-10-29 readme update
2020-10-29 KeyMap
2020-10-30 pins
2020-10-31 top plate
2020-10-31 top part svg
2020-11-01 top svg
2020-11-09 screen raiser
2020-11-09 pictures
2020-11-09 cleanup
2020-11-10 LICENSE
2020-11-19 Simple splashscreen on device start
2020-12-28 .devcontainer support and new splash screen
2021-02-22 top underglow support, v1
2021-02-23 extra supports
2021-02-23 fixed missalignment
2021-02-24 bottom spacer start
2021-02-24 bottom
2021-02-24 STLs
2021-02-25 underglow working
2021-02-27 layer toggle -> layer hold
2021-02-28 small changes
2021-02-28 correct position
2021-03-01 change underglow color with buttons
2021-03-03 storage
2021-03-04 EEPROM to store settings
2021-03-04 proper setting and storing of underglow
2021-03-04 device name
2021-03-27 plate -> bottom
2021-04-05 started working on the case
2021-04-08 refining
2021-04-09 switched to normal CAD to see what im doing
2021-04-12 case progress
2021-04-13 case complete
2021-04-14 final case commit
2021-04-18 rainbow effect
2021-04-23 added a NoEffect to have no effect
2021-04-23 allow for programming mode over usb
2021-05-10 anti-flex
2021-05-10 remove submodules
2021-05-10 kp.pretty
2021-05-10 lib_tmk
2021-05-10 KiCad-SSD1306-128x64
2021-05-10 MX_Alps_Hybrid
2021-05-10 teensy.pretty
2021-05-10 teensy_library
2021-05-10 library fixes
2021-05-10 readme fix
2021-08-12 started improving the case
2021-08-24 1.5mm petg plate v0.5
2021-08-28 added spacer for usb hole
2021-08-29 added holes in switch plate to reach pcb holes (rgb mount)
2021-10-01 changed the anti-flex hight a little
2021-11-18 documentation
2022-01-05 added full plate 3d print
2022-01-17 Added new case and refactored directory structure to account for multiple case designs
2022-01-17 minor grammar edit
2022-01-17 fixed menu path for the customizer
2022-01-18 clarified information about picture
2022-01-18 clarified some comments in the openscad code
2022-01-18 Update README.md
    fixed image links
2022-05-07 lets just include the backup files
2022-09-02 added a second static effect so i can switch between my fav solid colors
